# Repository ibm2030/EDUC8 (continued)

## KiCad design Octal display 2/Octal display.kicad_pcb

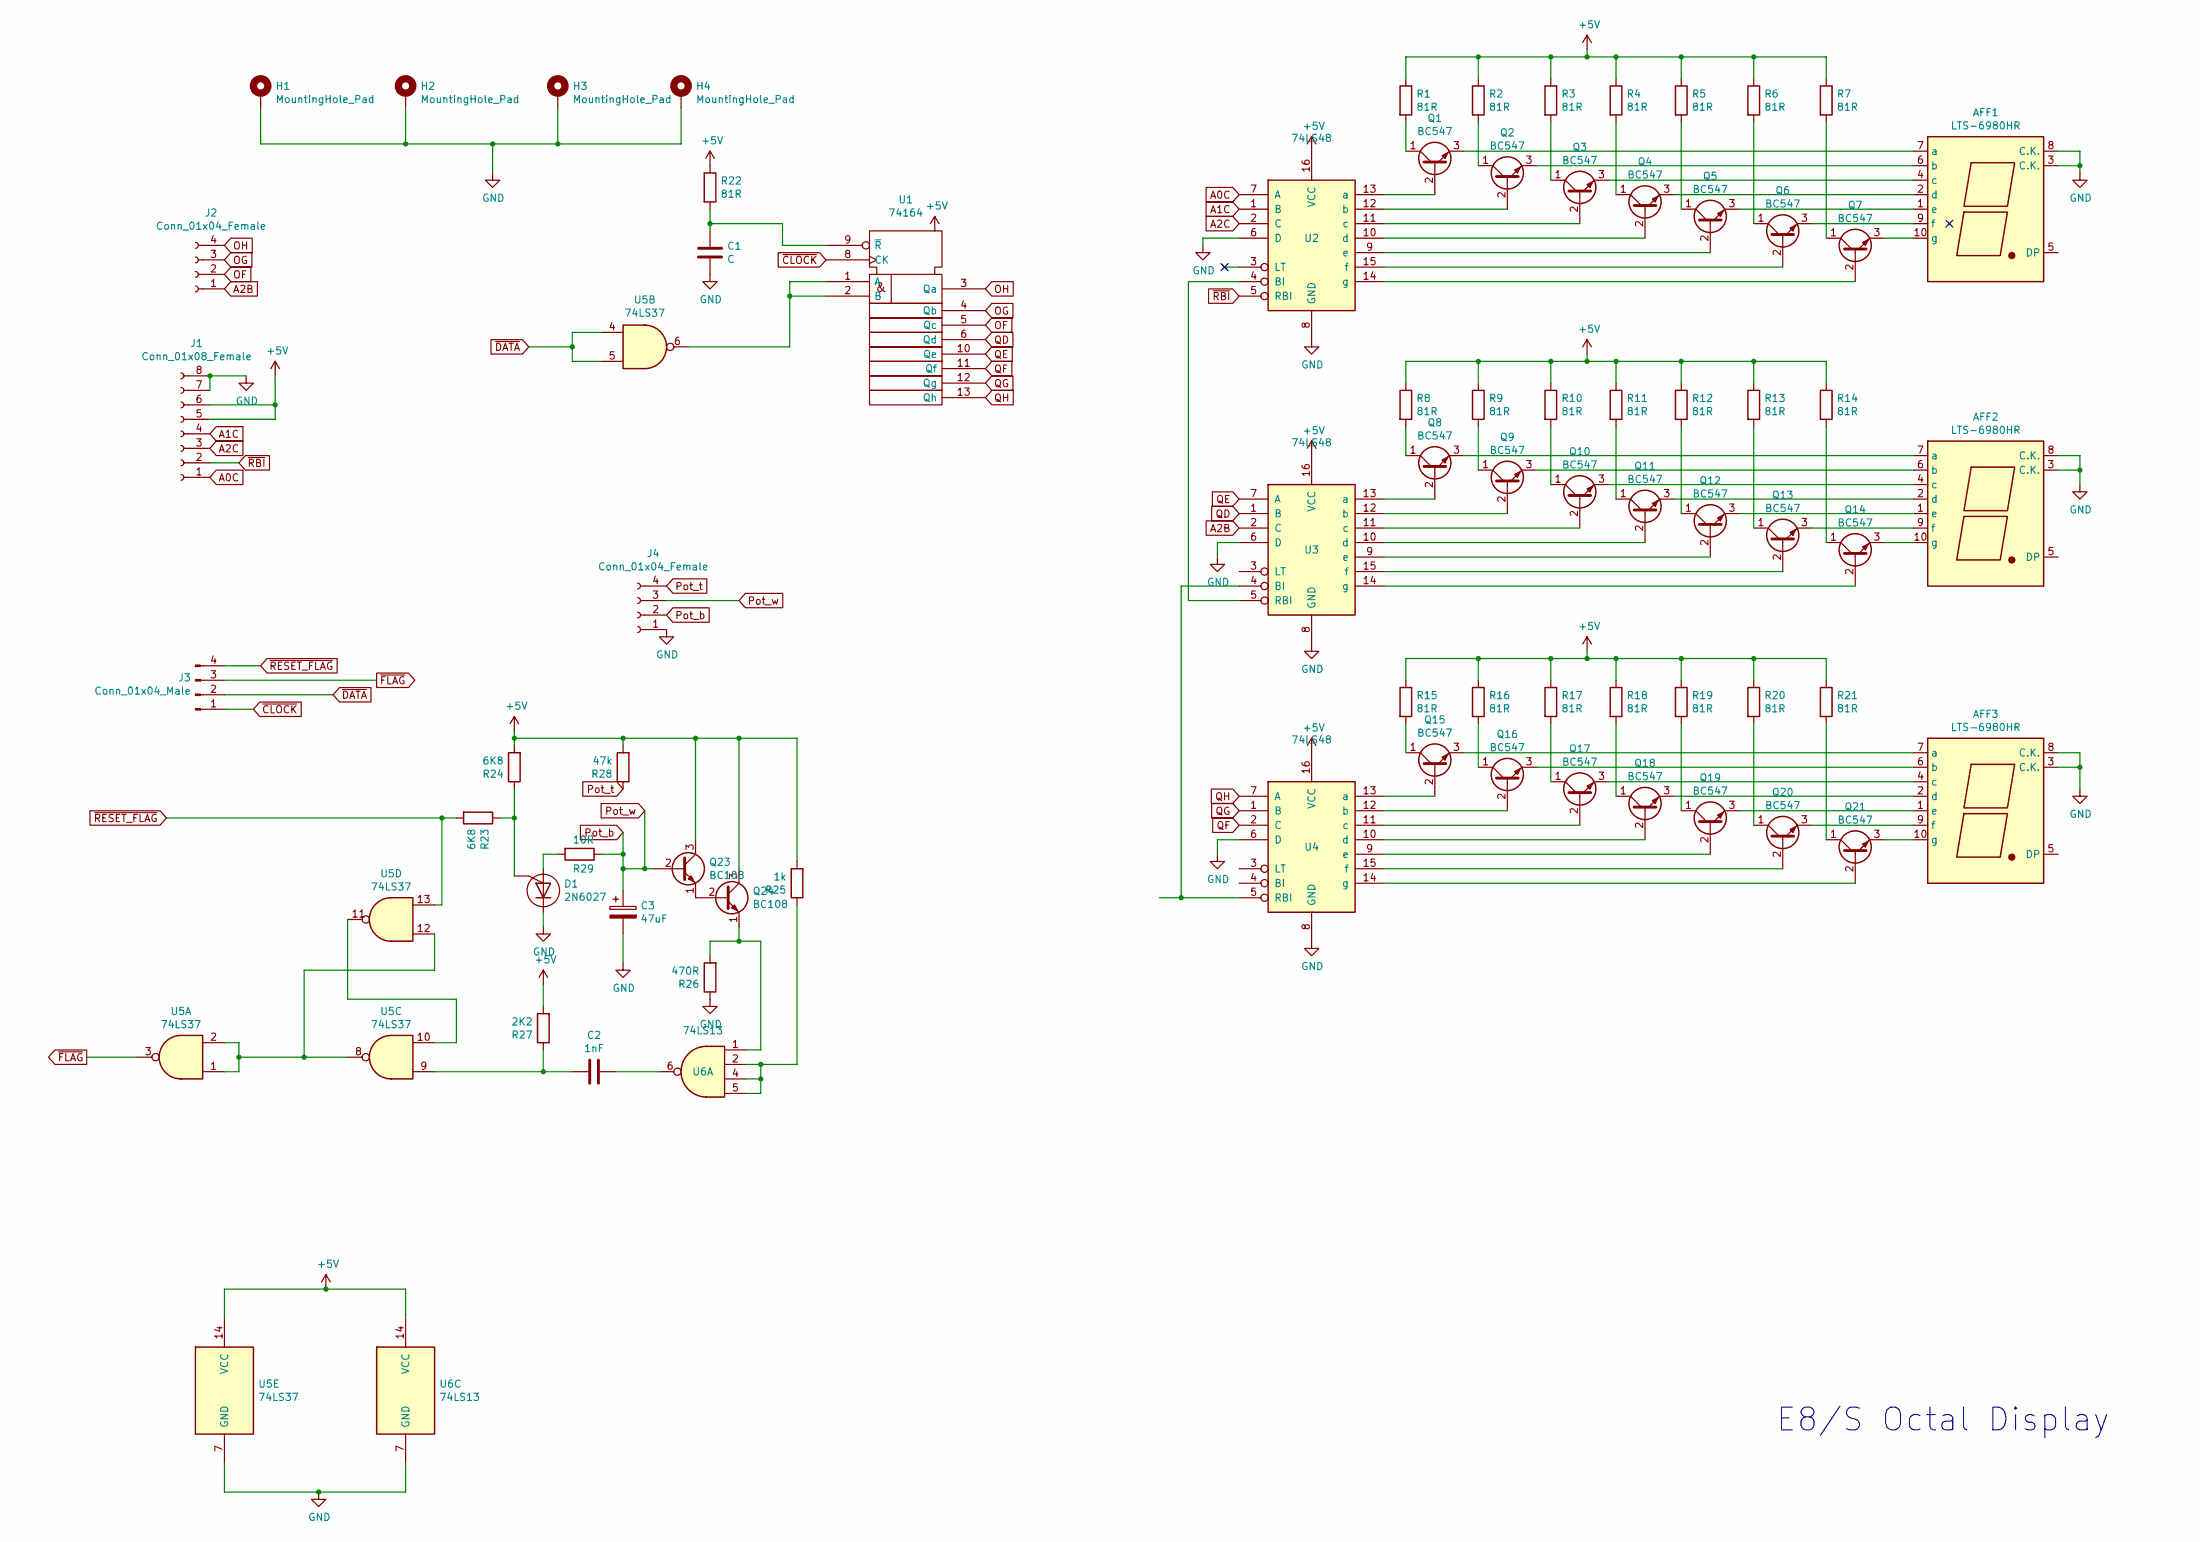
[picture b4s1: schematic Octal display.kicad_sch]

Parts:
AFF1, AFF2, AFF3: LTS-6980HR; 7SegmentLED_LTS6760_LTS6780
C1: C; C_Rect_L7.0mm_W2.5mm_P5.00mm
C2: 1nF; C_Disc_D5.0mm_W2.5mm_P5.00mm
C3: 47uF; CP_Radial_D5.0mm_P2.50mm
D1: 2N6027; TO-92_Inline_Wide
H1, H2, H3, H4: MountingHole_Pad; MountingHole_3.2mm_M3_Pad_Via
J1: Conn_01x08_Female; PinSocket_1x08_P2.54mm_Vertical
J2, J4: Conn_01x04_Female; PinSocket_1x04_P2.54mm_Vertical
J3: Conn_01x04_Male; PinSocket_1x04_P2.54mm_Vertical
Q1, Q2, Q3, Q4, Q5, Q6, Q7, Q8, Q9, Q10, Q11, Q12, Q13, Q14, Q15, Q16, Q17, Q18, Q19, Q20, Q21: BC547; TO-92_Inline_Wide
Q23, Q24: BC108; TO-18-3
R1, R2, R3, R4, R5, R6, R7, R8, R9, R10, R11, R12, R13, R14, R15, R16, R17, R18, R19, R20, R21, R22: 81R; R_Axial_DIN0207_L6.3mm_D2.5mm_P10.16mm_Horizontal
R23, R24: 6K8; R_Axial_DIN0207_L6.3mm_D2.5mm_P10.16mm_Horizontal
R25: 1k; R_Axial_DIN0207_L6.3mm_D2.5mm_P10.16mm_Horizontal
R26: 470R; R_Axial_DIN0207_L6.3mm_D2.5mm_P10.16mm_Horizontal
R27: 2K2; R_Axial_DIN0207_L6.3mm_D2.5mm_P10.16mm_Horizontal
R28: 47k; R_Axial_DIN0207_L6.3mm_D2.5mm_P10.16mm_Horizontal
R29: 10R; R_Axial_DIN0207_L6.3mm_D2.5mm_P10.16mm_Horizontal
U1: 74164; DIP-14_W7.62mm_LongPads
U2, U3, U4: 74LS48; DIP-16_W7.62mm
U5: 74LS37; DIP-14_W7.62mm
U6: 74LS13; DIP-14_W7.62mm

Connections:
+5V: J1.5, J1.6, Q23.3 (C), Q24.3 (C), R1.1, R2.1, R3.1, R4.1, R5.1, R6.1, R7.1, R8.1, R9.1, R10.1, R11.1, R12.1, R13.1, R14.1, R15.1, R16.1, R17.1, R18.1, R19.1, R20.1, R21.1, R22.1, R24.2, R25.2, R27.2, R28.2, U1.14 (Vdd), U2.16 (VCC), U3.16 (VCC), U4.16 (VCC), U5.14 (VCC), U6.14 (VCC)
A0C: J1.1, U2.7 (A)
A1C: J1.4, U2.1 (B)
A2B: J2.1, U3.2 (C)
A2C: J1.3, U2.2 (C)
GND: AFF1.3 (C.K.), AFF1.8 (C.K.), AFF2.3 (C.K.), AFF2.8 (C.K.), AFF3.3 (C.K.), AFF3.8 (C.K.), C1.2, C3.2, D1.3 (K), H1.1, H2.1, H3.1, H4.1, J1.7, J1.8, J4.1, R26.1, U2.6 (D), U2.8 (GND), U3.6 (D), U3.8 (GND), U4.6 (D), U4.8 (GND), U5.7 (GND), U6.7 (GND)
unnamed: AFF1.1 (e), Q5.3 (E)
unnamed: AFF1.2 (d), Q4.3 (E)
unnamed: AFF1.4 (c), Q3.3 (E)
unnamed: AFF1.6 (b), Q2.3 (E)
unnamed: AFF1.7 (a), Q1.3 (E)
unnamed: AFF1.9 (f), Q6.3 (E)
unnamed: AFF1.10 (g), Q7.3 (E)
unnamed: AFF2.1 (e), Q12.3 (E)
unnamed: AFF2.2 (d), Q11.3 (E)
unnamed: AFF2.4 (c), Q10.3 (E)
unnamed: AFF2.6 (b), Q9.3 (E)
unnamed: AFF2.7 (a), Q8.3 (E)
unnamed: AFF2.9 (f), Q13.3 (E)
unnamed: AFF2.10 (g), Q14.3 (E)
unnamed: AFF3.1 (e), Q19.3 (E)
unnamed: AFF3.2 (d), Q18.3 (E)
unnamed: AFF3.4 (c), Q17.3 (E)
unnamed: AFF3.6 (b), Q16.3 (E)
unnamed: AFF3.7 (a), Q15.3 (E)
unnamed: AFF3.9 (f), Q20.3 (E)
unnamed: AFF3.10 (g), Q21.3 (E)
unnamed: C1.1, R22.2, U1.9 (~R)
unnamed: C2.1, U6.6
unnamed: C2.2, R27.1, U5.9
unnamed: D1.1 (A), R29.2
unnamed: D1.2 (G), R23.1, R24.1
unnamed: Q1.1 (C), R1.2
unnamed: Q1.2 (B), U2.13 (a)
unnamed: Q2.1 (C), R2.2
unnamed: Q2.2 (B), U2.12 (b)
unnamed: Q3.1 (C), R3.2
unnamed: Q3.2 (B), U2.11 (c)
unnamed: Q4.1 (C), R4.2
unnamed: Q4.2 (B), U2.10 (d)
unnamed: Q5.1 (C), R5.2
unnamed: Q5.2 (B), U2.9 (e)
unnamed: Q6.1 (C), R6.2
unnamed: Q6.2 (B), U2.15 (f)
unnamed: Q7.1 (C), R7.2
unnamed: Q7.2 (B), U2.14 (g)
unnamed: Q8.1 (C), R8.2
unnamed: Q8.2 (B), U3.13 (a)
unnamed: Q9.1 (C), R9.2
unnamed: Q9.2 (B), U3.12 (b)
unnamed: Q10.1 (C), R10.2
unnamed: Q10.2 (B), U3.11 (c)
unnamed: Q11.1 (C), R11.2
unnamed: Q11.2 (B), U3.10 (d)
unnamed: Q12.1 (C), R12.2
unnamed: Q12.2 (B), U3.9 (e)
unnamed: Q13.1 (C), R13.2
unnamed: Q13.2 (B), U3.15 (f)
unnamed: Q14.1 (C), R14.2
unnamed: Q14.2 (B), U3.14 (g)
unnamed: Q15.1 (C), R15.2
unnamed: Q15.2 (B), U4.13 (a)
unnamed: Q16.1 (C), R16.2
unnamed: Q16.2 (B), U4.12 (b)
unnamed: Q17.1 (C), R17.2
unnamed: Q17.2 (B), U4.11 (c)
unnamed: Q18.1 (C), R18.2
unnamed: Q18.2 (B), U4.10 (d)
unnamed: Q19.1 (C), R19.2
unnamed: Q19.2 (B), U4.9 (e)
unnamed: Q20.1 (C), R20.2
unnamed: Q20.2 (B), U4.15 (f)
unnamed: Q21.1 (C), R21.2
unnamed: Q21.2 (B), U4.14 (g)
unnamed: Q23.1 (E), Q24.2 (B)
unnamed: Q24.1 (E), R26.2, U6.1
unnamed: R25.1, U6.2, U6.4, U6.5
unnamed: U1.1 (A), U1.2 (B), U5.6
unnamed: U2.4 (BI), U3.5 (RBI)
unnamed: U3.4 (BI), U4.5 (RBI)
unnamed: U5.1, U5.2, U5.8, U5.12
unnamed: U5.10, U5.11
OF: J2.2, U1.5 (Qc)
OG: J2.3, U1.4 (Qb)
OH: J2.4, U1.3 (Qa)
Pot_b: C3.1, J4.2, J4.3, Q23.2 (B), R29.1
Pot_t: J4.4, R28.1
QD: U1.6 (Qd), U3.1 (B)
QE: U1.10 (Qe), U3.7 (A)
QF: U1.11 (Qf), U4.2 (C)
QG: U1.12 (Qg), U4.1 (B)
QH: U1.13 (Qh), U4.7 (A)
Vss: U1.7 (Vss)
~CLOCK: J3.1, U1.8 (CK)
~DATA: J3.2, U5.4, U5.5
~FLAG: J3.3, U5.3
~RBI: J1.2, U2.5 (RBI)
~RESET_FLAG: J3.4, R23.2, U5.13

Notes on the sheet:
E8/S Octal Display

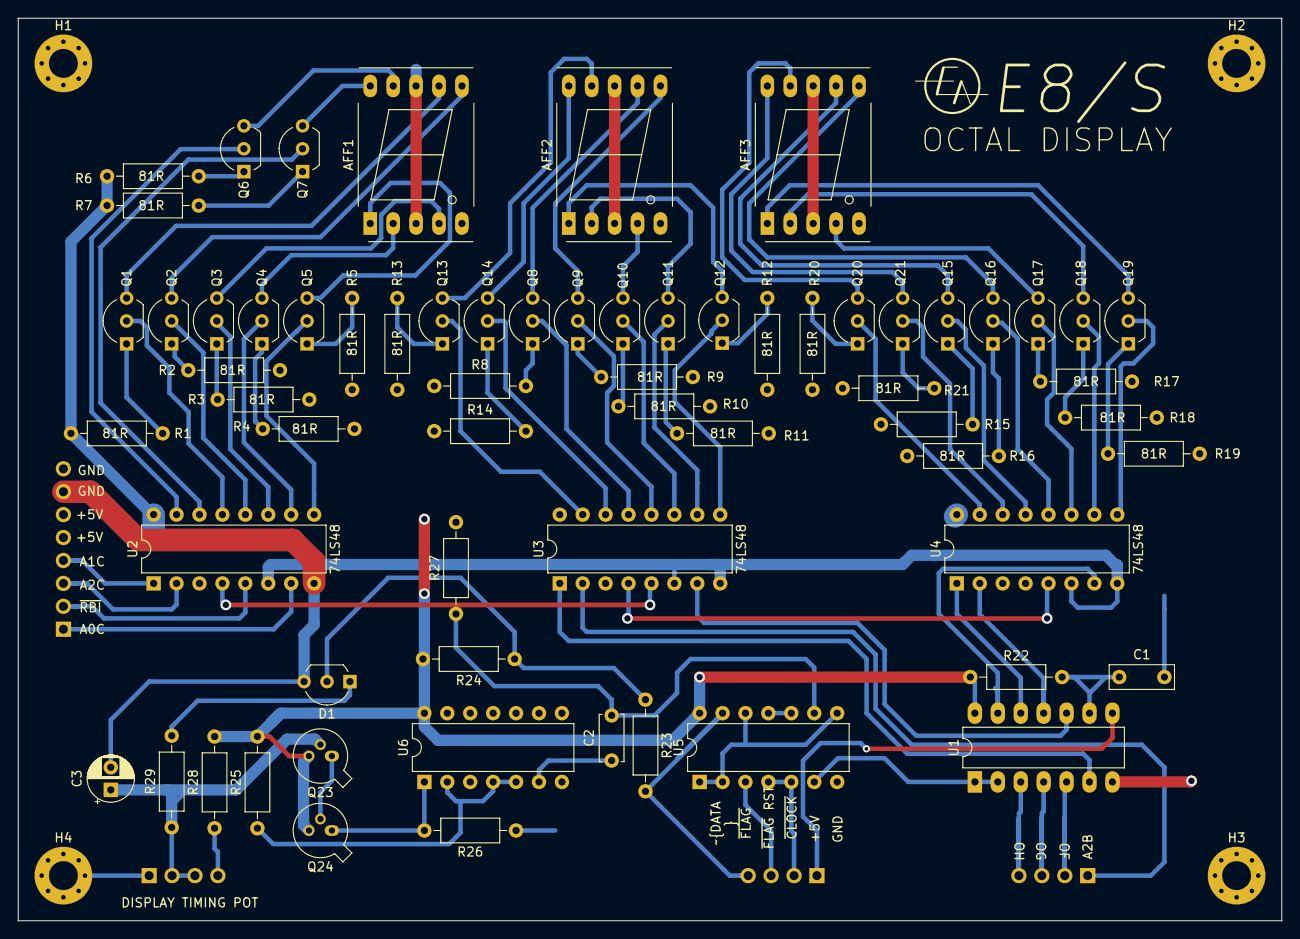
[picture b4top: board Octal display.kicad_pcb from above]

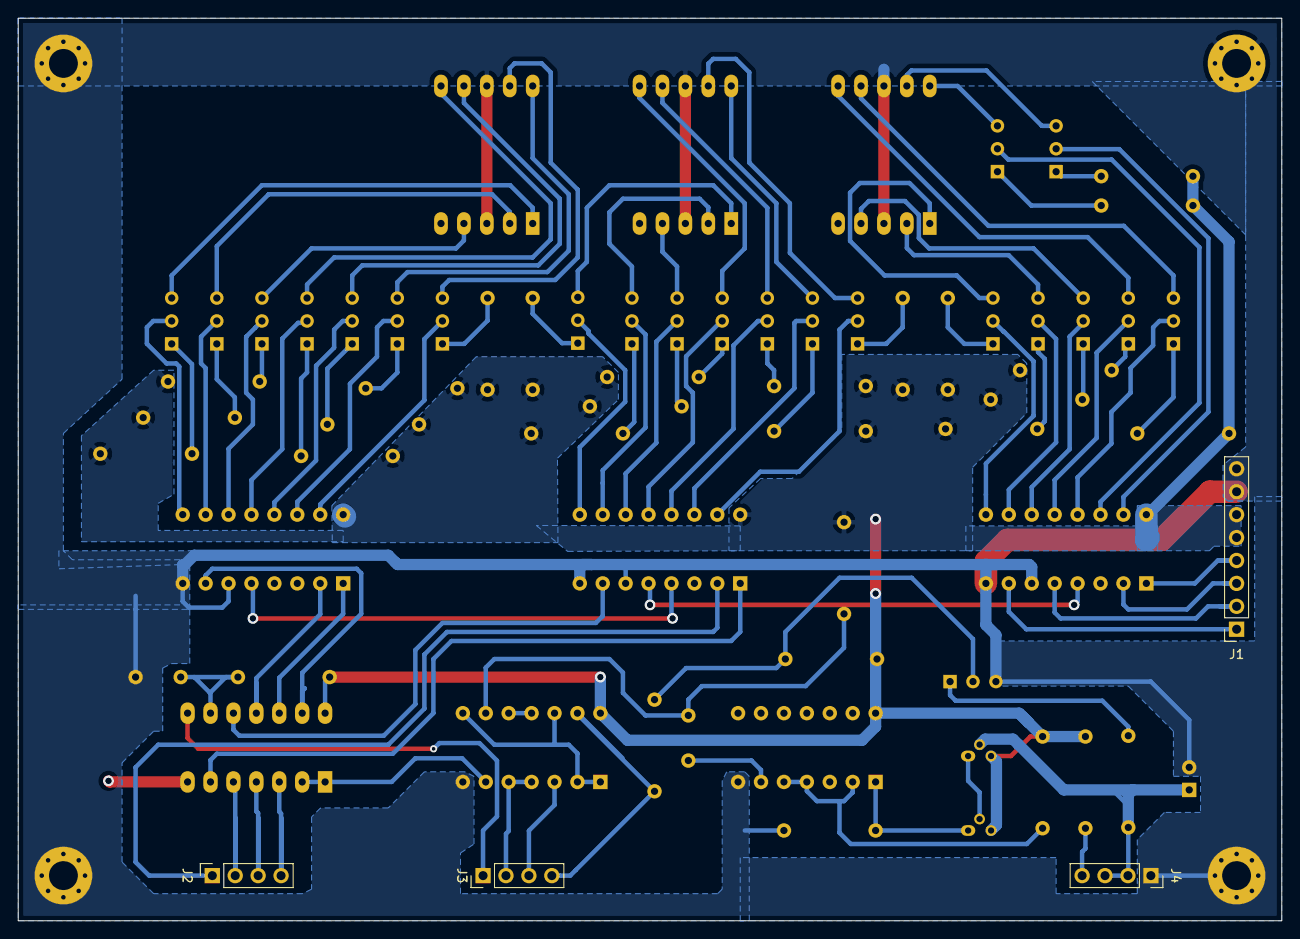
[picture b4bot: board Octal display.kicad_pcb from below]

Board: 2 copper layers, 140.0 x 100.0 mm, 73 parts (4 on the bottom side), 97 nets.

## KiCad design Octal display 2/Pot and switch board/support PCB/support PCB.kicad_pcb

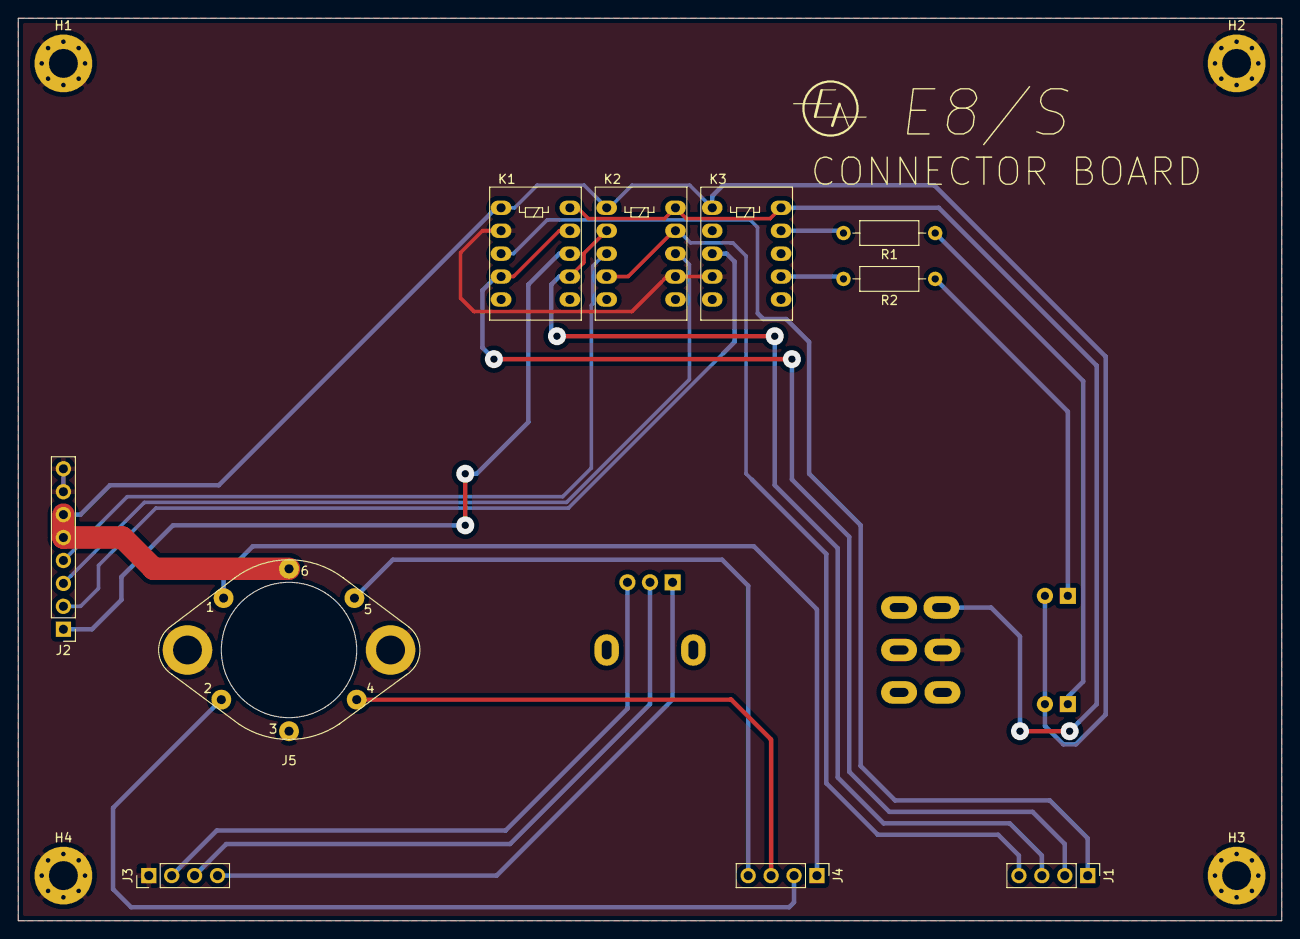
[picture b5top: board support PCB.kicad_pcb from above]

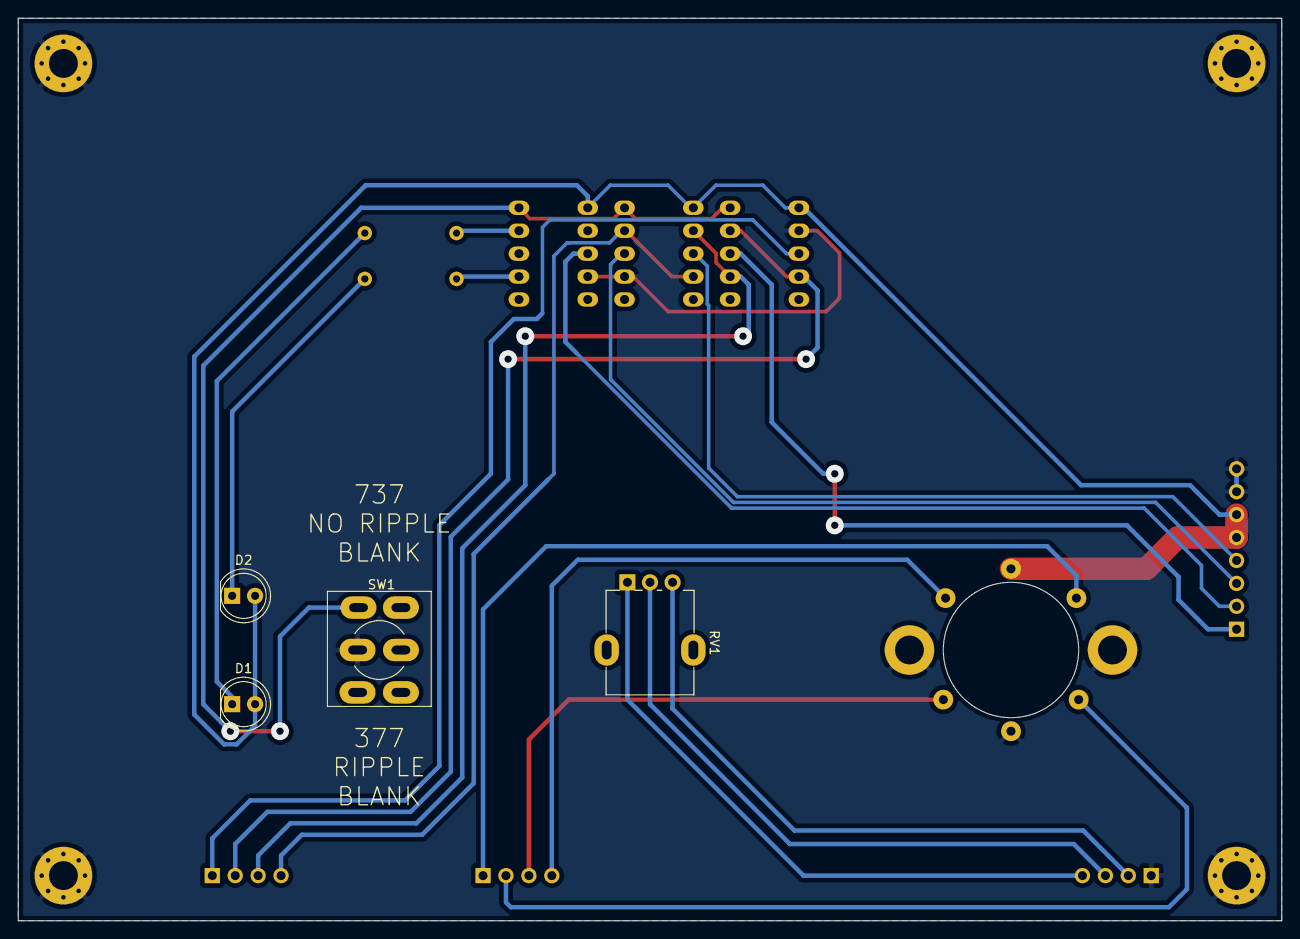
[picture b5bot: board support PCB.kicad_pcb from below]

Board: 2 copper layers, 140.0 x 100.0 mm, 18 parts (4 on the bottom side), 22 nets.

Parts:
D1: 377; LED_D5.0mm
D2: 737; LED_D5.0mm
H1, H2, H3, H4: MountingHole_Pad; MountingHole_3.2mm_M3_Pad_Via
J1, J3, J4: Conn_01x04_Male; PinHeader_1x04_P2.54mm_Vertical
J2: Conn_01x08_Male; PinHeader_1x08_P2.54mm_Vertical
J5: DIN-6_SH; 6_PIN_DIN_SOCKET
K1, K2, K3: FRT5; Relay_DPDT_FRT5
R1, R2: R; R_Axial_DIN0207_L6.3mm_D2.5mm_P10.16mm_Horizontal
RV1: R_POT; Potentiometer_Alpha_RD901F-40-00D_Single_Vertical
SW1: SW_DPDT_x2; DPDT_toggle_switch_wired

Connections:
+5V: D1.2, D2.2, J2.5, J2.6, J5.6, K1.1, K2.1, K3.1
A0C: J2.1, K1.8
A1C: J2.4, K2.3
A2B: J1.1, K1.3
A2C: J2.3, K2.8
GND: H1.1, H2.1, H3.1, H4.1, J2.7, J2.8, J3.1, J5.0, J5.3, K1.2, K2.7, K3.4, SW1.2
unnamed: D1.1, R1.1
unnamed: D2.1, R2.1
unnamed: J3.2, RV1.3
unnamed: J3.3, RV1.2
unnamed: J3.4, RV1.1
unnamed: K1.10, K2.10, K3.8, K3.10, SW1.3
unnamed: K3.7, R2.2
unnamed: K3.9, R1.2
OF: J1.2, K1.4, K1.9
OG: J1.3, K1.7, K2.2
OH: J1.4, K2.4, K2.9
~CLOCK: J4.1, J5.1
~DATA: J4.2, J5.2
~FLAG_RESET: J4.4, J5.5
~FLAG: J4.3, J5.4
~RBI: J2.2, K3.3
